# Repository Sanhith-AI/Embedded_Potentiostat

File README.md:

# Embedded_Potentiostat
This project mainly focuses on the development and testing of an embedded potentiostat system that can perform electrochemistry methods like Cyclic voltammetry, Square wave voltammetry, Differential pulse voltammetry, and Impedance spectroscopy.
This project includes the circuit design and PCB design of a potentiostat and power supply using Eagle Autodesk software.
The software implementation includes driver development for SPI, UART, TIMERS, DACs, and ADCs of the STM32F303ZETx microcontroller using STM32cubeIDE as well as Eclipse IDE. Along with driver development, electrochemical methods and digital signal processing methods were implemented using a microcontroller and Matlab.
Moreover, a graphic user interface (GUI) was implemented using C# and Visual Studio to automate the measurement process of the developed potentiostat.

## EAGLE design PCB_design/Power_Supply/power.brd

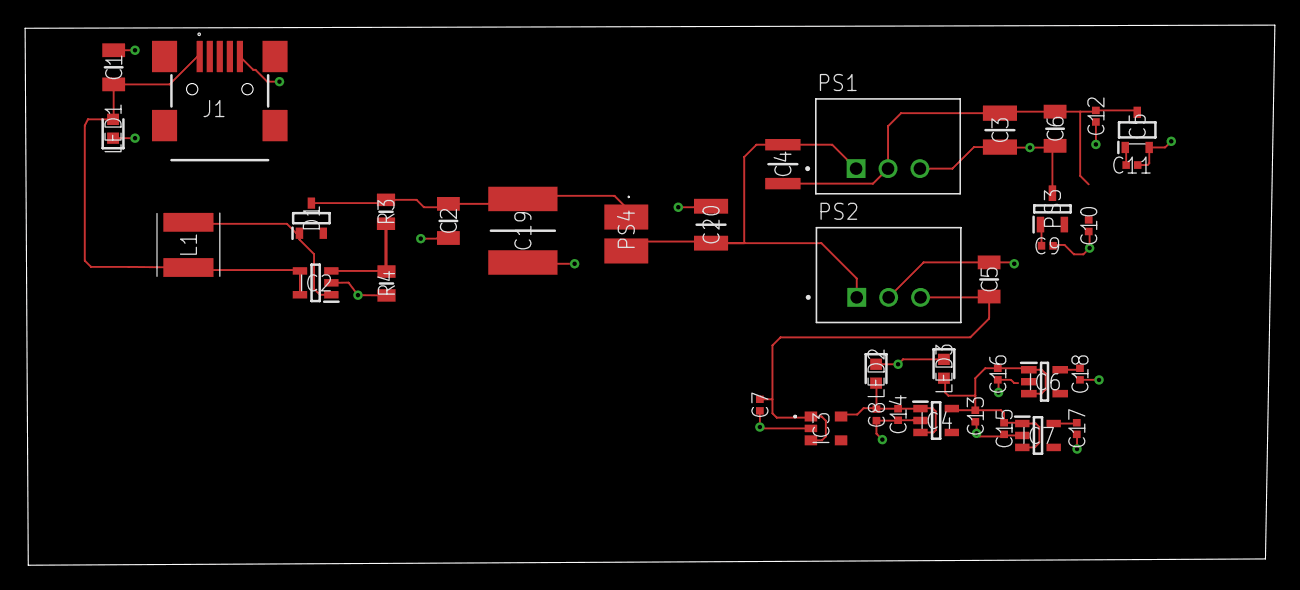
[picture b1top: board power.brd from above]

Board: 2 copper layers, 99.5 x 43.0 mm, 38 parts (0 on the bottom side), 14 nets.

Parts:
C1, C2, C5, C6: LMF316AB7475KLHT; CAPC3216X180N
C3: LMF325B7106KMHP; CAPC3225X270N
C4: GRJ32ER71H106KE11L; CAPC3225X280N
C7, C8, C9, C10, C11, C12, C13, C14, C15, C16, C17, C18: GRM155R70J105KA12D; CAPC1005X55N
C19: KRM55QR72A106KH01L; CAPC6153X390N
C20: 12101C335KAT2A; CAPC3325X279N
D1: BAT54CHYFHT116; SOT95P240X115-3N
IC2: LM2703MFX-ADJ_NOPB; SOT95P280X145-5N
IC3: TCR2EF50,LM_CT; TCR2EF50LMCT
IC4: ADM7160AUJZ-2.5-R7; SOT95P280X100-5N
IC5: XC6902N251MR-G; SOT95P280X130-3N
IC6: NCV8114ASN165T1G; SOT95P275X110-5N
IC7: NCP163ASN150T1G; SOT95P280X145-5N
J1: 65100516121
L1: VLS5045EX-100M-H; VLS5045EX330M
LED1, LED2: LT_Q39G-Q1OO-25-1; LEDC1608X40N
LED3: LB_Q39E-N1OO-35-1; LEDC1608X40N
PS1, PS2: R-786.5-0.5; CONV_R-786.5-0.5
PS3: TC595002ECBTR; SOT95P275X130-3N
PS4: RLS-397; RLS397
R3, R4: TNPW080527K4BEEN; RESC2012X55N

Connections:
1.5V: C17.1, IC7.5
1.65V: C18.1, IC6.5
2.5V: C13.1, C15.1, C16.1, IC4.5, IC6.1, IC6.3, IC7.1, IC7.3, LED3.2
5V: C8.1, C14.1, IC3.5, IC4.1, IC4.3, LED2.2
6.5V: C5.1, C7.1, IC3.1, IC3.3, PS2.3
-2.5V: C11.1, IC5.1
-5V: C9.2, PS3.1
-6.5V: C3.2, C4.2, C6.1, C10.2, C12.1, IC5.3, PS1.2, PS3.2
GND: C1.2, C2.2, C3.1, C5.2, C6.2, C7.2, C8.2, C9.1, C10.1, C11.2, C12.2, C13.2, C14.2, C15.2, C16.2, C17.2, C18.2, C19.2, C20.2, IC2.2, IC3.2, IC4.2, IC5.2, IC7.2, J1.5, LED1.1, LED2.1, LED3.1, PS1.3, PS2.2, PS3.3, R4.2
IN: C2.1, C19.1, D1.3, PS4.1, R3.2
unnamed: IC2.3, R3.1, R4.1
unnamed: C4.1, C20.1, PS1.1, PS2.1, PS4.2
unnamed: D1.1, IC2.1, L1.2
VIN: C1.1, IC2.4, IC2.5, J1.1, L1.1, LED1.2

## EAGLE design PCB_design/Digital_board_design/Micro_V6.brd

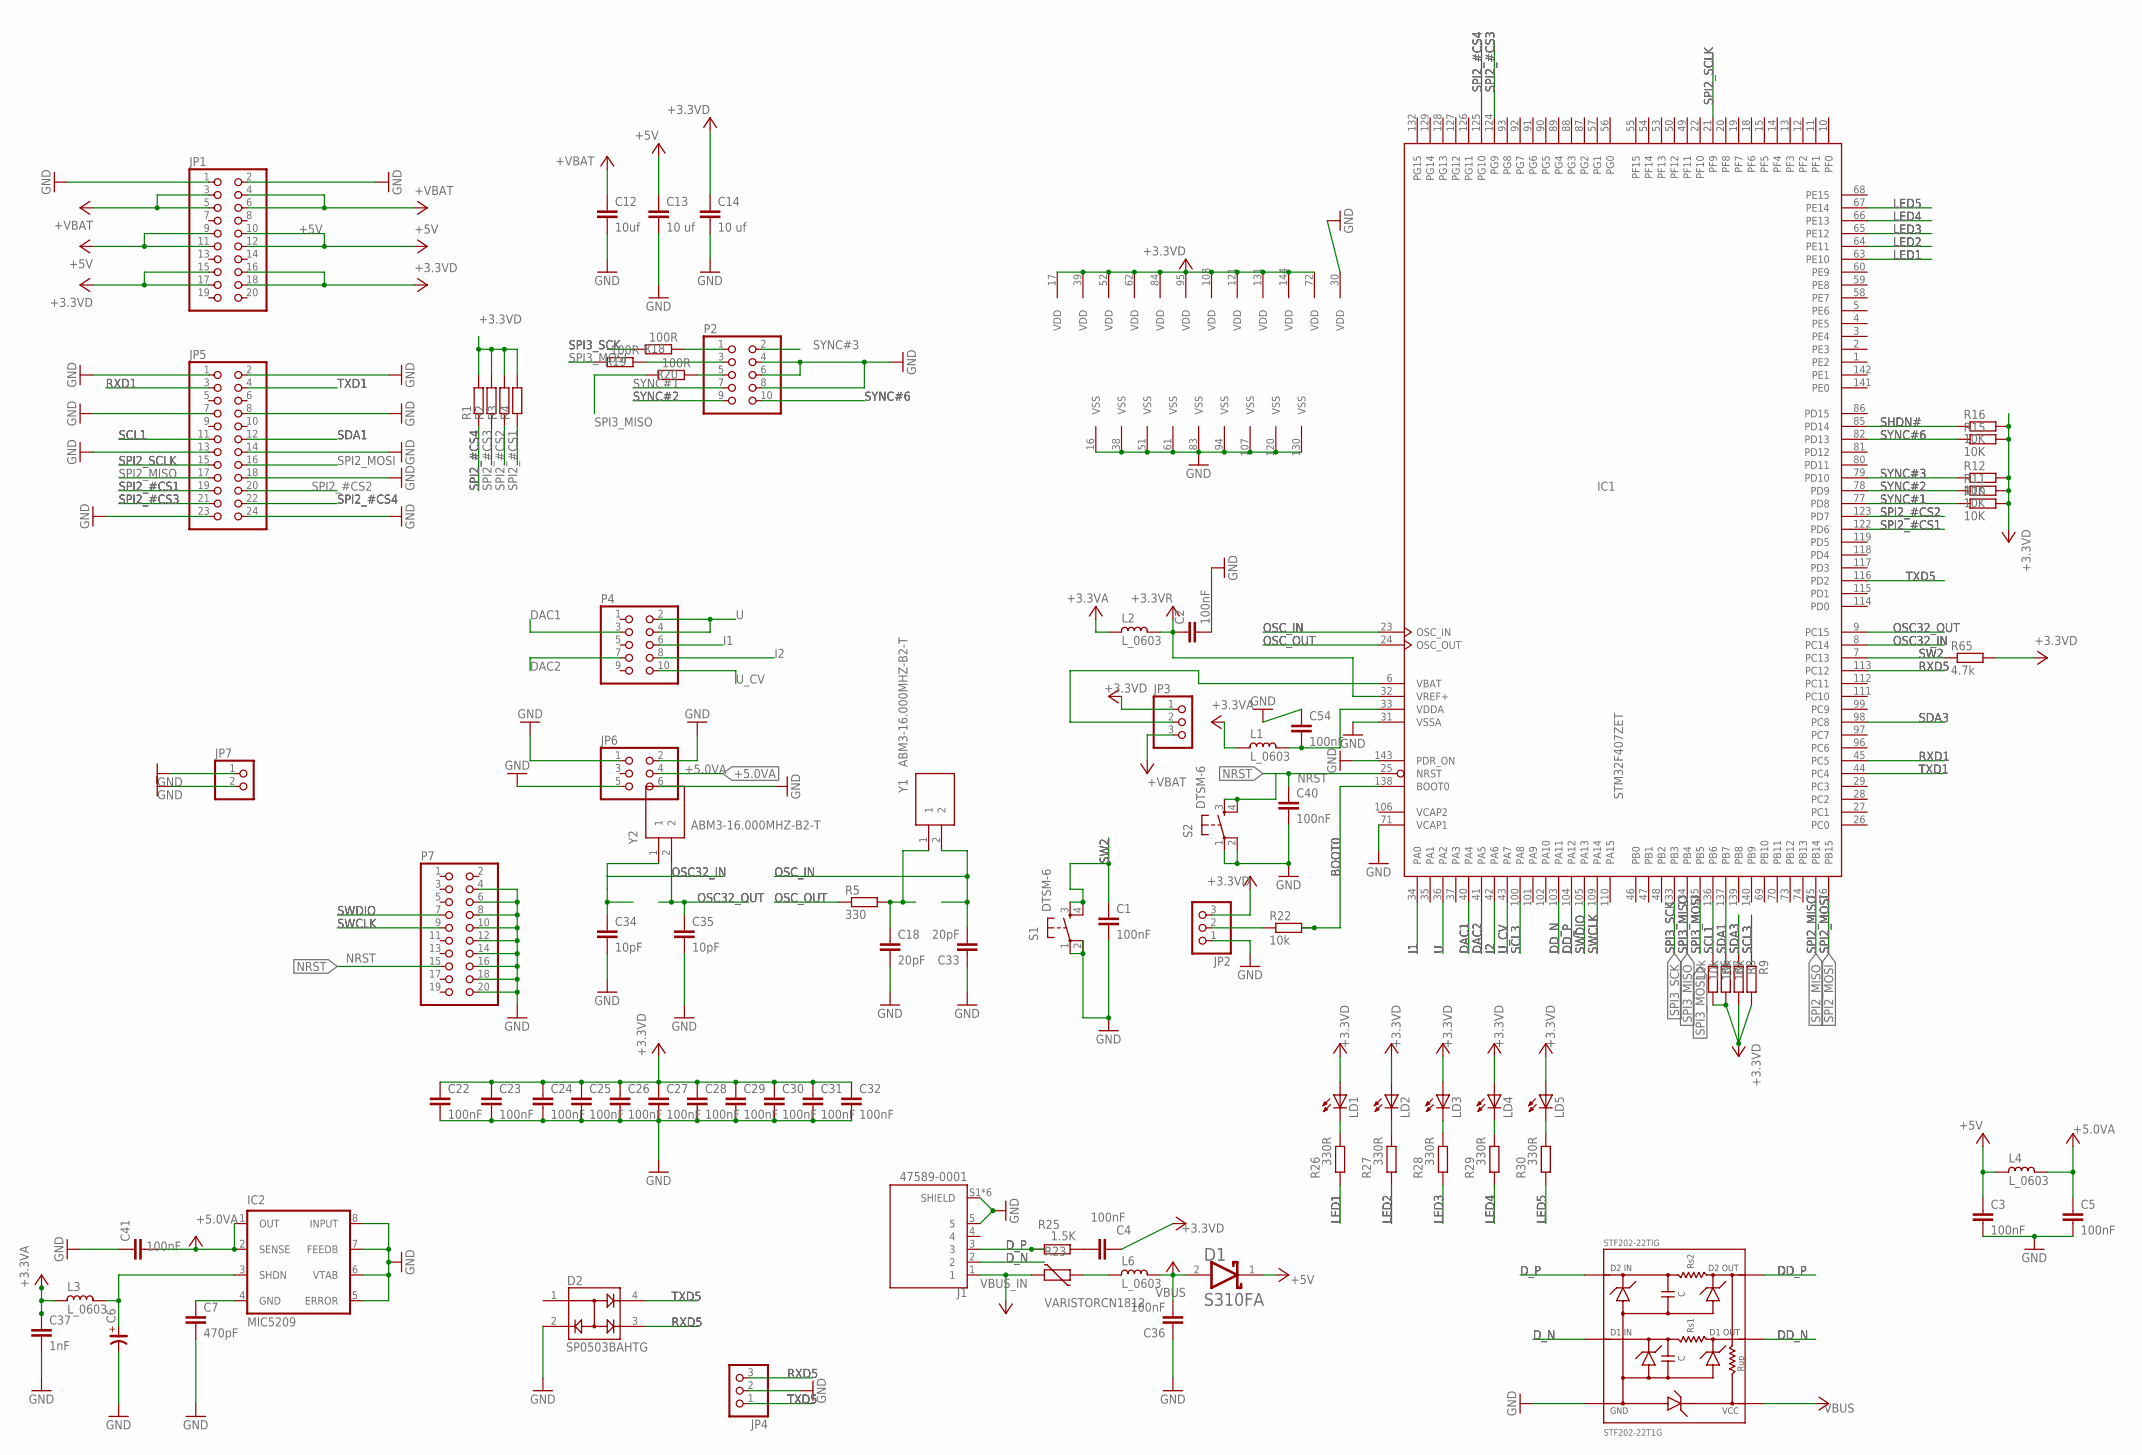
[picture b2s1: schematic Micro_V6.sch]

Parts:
C1, C2, C3, C4, C5, C22, C23, C24, C25, C26, C27, C28, C29, C30, C31, C32, C36, C40, C41, C54: 100nF; C0805
C6: CP_SV-A; CSV-A
C7: 470pF; C0805
C12: 10uf; C0805K
C13, C14: 10 uf; C0805K
C18, C33: 20pF; C0805
C34, C35: 10pF; C0805
C37: 1nF; C0805
D1: ON_SEMICONDUCTOR_S310FAON_SEMICONDUCTOR_S310FA_0_0; ON_SEMICONDUCTOR_S310FA_0
D2: SP0503BAHTG; SOT143
IC1: STM32F407ZET; LQFP144
IC2: MIC5209; SO-08
J1: 47589-0001; MOLEX_47589-0001
JP1: PINHD-2X10; 2X10
JP2, JP3, JP4: PINHD-1X3; 1X03
JP5: PINHD-2X12; 2X12
JP6: PINHD-2X3; 2X03
JP7: PINHD-1X2; 1X02
L1, L2, L3, L4, L6: L_0603; L0603
LD1, LD2, LD3, LD4, LD5: LEDSMT1206; 1206
P2, P4: PINHD-2X5; 2X05
P7: PINHD-2X10; 2X10
R1, R2, R3, R4: R-EU_R0603; R0603
R5: 330; R0603
R6, R7, R8, R9, R22: 10k; R0603
R10, R11, R12, R15, R16: 10K; R0603
R18, R19, R20: 100R; R0603
R23: VARISTORCN1812; CT/CN1812
R25: 1.5K; R0603
R26, R27, R28, R29, R30: 330R; R0603
R65: 4.7k; R0603
S1, S2: DTSM-6
STF202-22TIG: STF202-22T1G
Y1, Y2: ABM3-16.000MHZ-B2-T; ABM316000MHZB2T

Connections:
+3.3VA: C37.1, L1.2, L2.2, L3.2
+3.3VD: C4.1, C14.1, C22.1, C23.1, C24.1, C25.1, C26.1, C27.1, C28.1, C29.1, C30.1, C31.1, C32.1, IC1.17 (VDD), IC1.39 (VDD), IC1.52 (VDD), IC1.62 (VDD), IC1.72 (VDD), IC1.84 (VDD), IC1.95 (VDD), IC1.108 (VDD), IC1.121 (VDD), IC1.131 (VDD), IC1.144 (VDD), JP1.15, JP1.16, JP1.17, JP1.18, JP2.3, JP3.1, LD1.A, LD2.A, LD3.A, LD4.A, LD5.A, R1.2, R2.2, R3.2, R4.2, R6.2, R7.2, R8.2, R9.2, R10.2, R11.2, R12.2, R15.2, R16.2, R65.2
+3.3VR: C2.1, IC1.32 (VREF+), L2.1
+5.0VA: C5.1, C41.2, IC2.1 (OUT), IC2.2 (SENSE), JP6.4, L4.1
+5V: C3.1, C13.1, D1.1 (CATHODE), JP1.9, JP1.10, JP1.11, JP1.12, L4.2
+VBAT: C12.1, JP1.3, JP1.4, JP1.5, JP1.6, JP3.3
BOOT0: IC1.138 (BOOT0), R22.2
DAC1: IC1.40 (PA4), P4.3
DAC2: IC1.41 (PA5), P4.7
DD_N: IC1.103 (PA11), STF202-22TIG.2 (D1-IN)
DD_P: IC1.104 (PA12), STF202-22TIG.3 (D2-IN)
D_N: J1.2, STF202-22TIG.5 (D1-OUT)
D_P: J1.3, R25.1, STF202-22TIG.4 (D2-OUT)
GND: C1.2, C2.2, C3.2, C5.2, C6.-, C7.2, C12.2, C13.2, C14.2, C18.2, C22.2, C23.2, C24.2, C25.2, C26.2, C27.2, C28.2, C29.2, C30.2, C31.2, C32.2, C33.1, C34.2, C35.2, C36.1, C37.2, C40.2, C41.1, C54.1, D2.2, IC1.16 (VSS), IC1.30 (VDD), IC1.31 (VSSA), IC1.38 (VSS), IC1.51 (VSS), IC1.61 (VSS), IC1.71 (VCAP1), IC1.83 (VSS), IC1.94 (VSS), IC1.107 (VSS), IC1.120 (VSS), IC1.130 (VSS), IC1.143 (PDR_ON), IC2.5 (ERROR), IC2.6 (VTAB), IC2.7 (FEEDB), IC2.8 (INPUT), J1.5, J1.S1 (SHIELD), J1.S2 (SHIELD), J1.S3 (SHIELD), J1.S4 (SHIELD), J1.S5 (SHIELD), J1.S6 (SHIELD), JP1.1, JP1.2, JP2.1, JP4.2, JP5.1, JP5.2, JP5.7, JP5.8, JP5.13, JP5.14, JP5.18, JP5.23, JP5.24, JP6.1, JP6.2, JP6.5, JP6.6, JP7.1, JP7.2, P2.4, P2.6, P2.8, P7.4, P7.6, P7.8, P7.10, P7.12, P7.14, P7.16, P7.18, P7.20, S1.1, S1.2, S2.1, S2.2, STF202-22TIG.6 (GND)
I1: IC1.34 (PA0), P4.6
I2: IC1.42 (PA6), P4.8
LED1: IC1.63 (PE10), R26.1
LED2: IC1.64 (PE11), R27.1
LED3: IC1.65 (PE12), R28.1
LED4: IC1.66 (PE13), R29.1
LED5: IC1.67 (PE14), R30.1
unnamed: IC1.6 (VBAT), JP3.2
unnamed: C54.2, IC1.33 (VDDA), L1.1
unnamed: P2.3, R19.1
unnamed: P2.5, R20.1
unnamed: L6.2, R23.1
unnamed: P2.1, R18.1
unnamed: C18.1, R5.2, Y1.1
unnamed: JP2.2, R22.1
unnamed: C6.+, IC2.3 (SHDN), L3.1
unnamed: C7.1, IC2.4 (GND)
unnamed: C4.2, R25.2
unnamed: LD1.C, R26.2
unnamed: LD2.C, R27.2
unnamed: LD3.C, R28.2
unnamed: LD4.C, R29.2
unnamed: LD5.C, R30.2
NRST: C40.1, IC1.25 (NRST), P7.15, S2.3, S2.4
OSC32_IN: C34.1, IC1.8 (PC14), Y2.1
OSC32_OUT: C35.1, IC1.9 (PC15), Y2.2
OSC_IN: C33.2, IC1.23 (OSC_IN), Y1.2
OSC_OUT: IC1.24 (OSC_OUT), R5.1
RXD1: IC1.45 (PC5), JP5.3
RXD5: D2.3, IC1.113 (PC12), JP4.3
SCL1: IC1.136 (PB6), JP5.11, R6.1
SCL3: IC1.100 (PA8), R9.1
SDA1: IC1.137 (PB7), JP5.12, R7.1
SDA3: IC1.98 (PC8), R8.1
SHDN#: IC1.85 (PD14), R16.1
SPI2_#CS1: IC1.122 (PD6), JP5.19, R4.1
SPI2_#CS2: IC1.123 (PD7), JP5.20, R3.1
SPI2_#CS3: IC1.124 (PG9), JP5.21, R2.1
SPI2_#CS4: IC1.125 (PG10), JP5.22, R1.1
SPI2_MISO: IC1.75 (PB14), JP5.17
SPI2_MOSI: IC1.76 (PB15), JP5.16
SPI2_SCLK: IC1.21 (PF9), JP5.15
SPI3_MISO: IC1.134 (PB4), R20.2
SPI3_MOSI: IC1.135 (PB5), R19.2
SPI3_SCK: IC1.133 (PB3), R18.2
SW2: C1.1, IC1.7 (PC13), R65.1, S1.3, S1.4
SWCLK: IC1.109 (PA14), P7.9
SWDIO: IC1.105 (PA13), P7.7
SYNC#1: IC1.77 (PD8), P2.7, R10.1
SYNC#2: IC1.78 (PD9), P2.9, R11.1
SYNC#3: IC1.79 (PD10), P2.2, R12.1
SYNC#6: IC1.82 (PD13), P2.10, R15.1
TXD1: IC1.44 (PC4), JP5.4
TXD5: D2.4, IC1.116 (PD2), JP4.1
U: IC1.36 (PA2), P4.2, P4.4
U_CV: IC1.43 (PA7), P4.10
VBUS: C36.2, D1.2 (ANODE), L6.1, STF202-22TIG.1 (VCC)
VBUS_IN: J1.1, R23.2
VCAP2: IC1.106 (VCAP2)

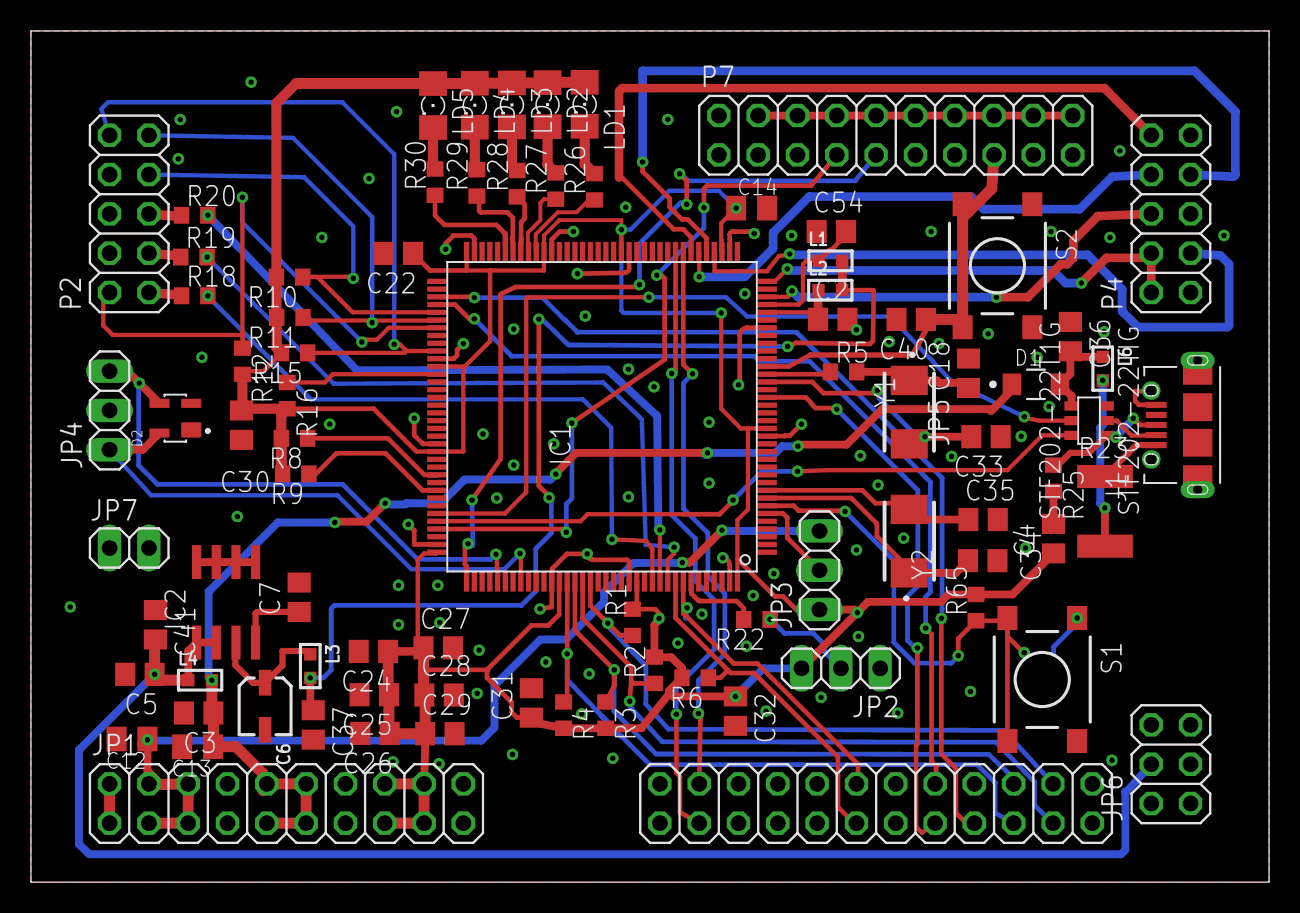
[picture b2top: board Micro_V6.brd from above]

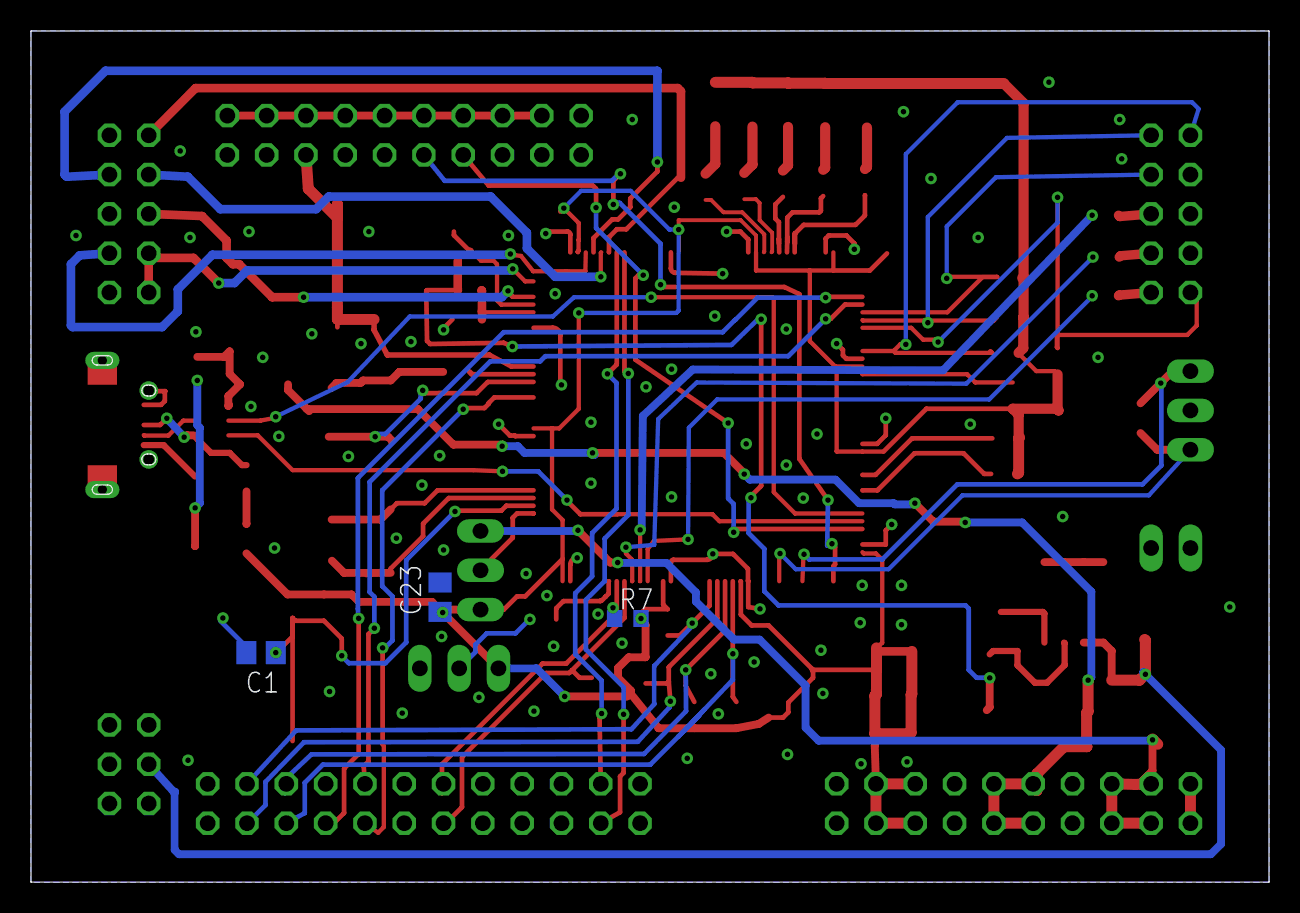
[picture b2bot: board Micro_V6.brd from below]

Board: 2 copper layers, 80.0 x 55.0 mm, 86 parts (3 on the bottom side), 72 nets.

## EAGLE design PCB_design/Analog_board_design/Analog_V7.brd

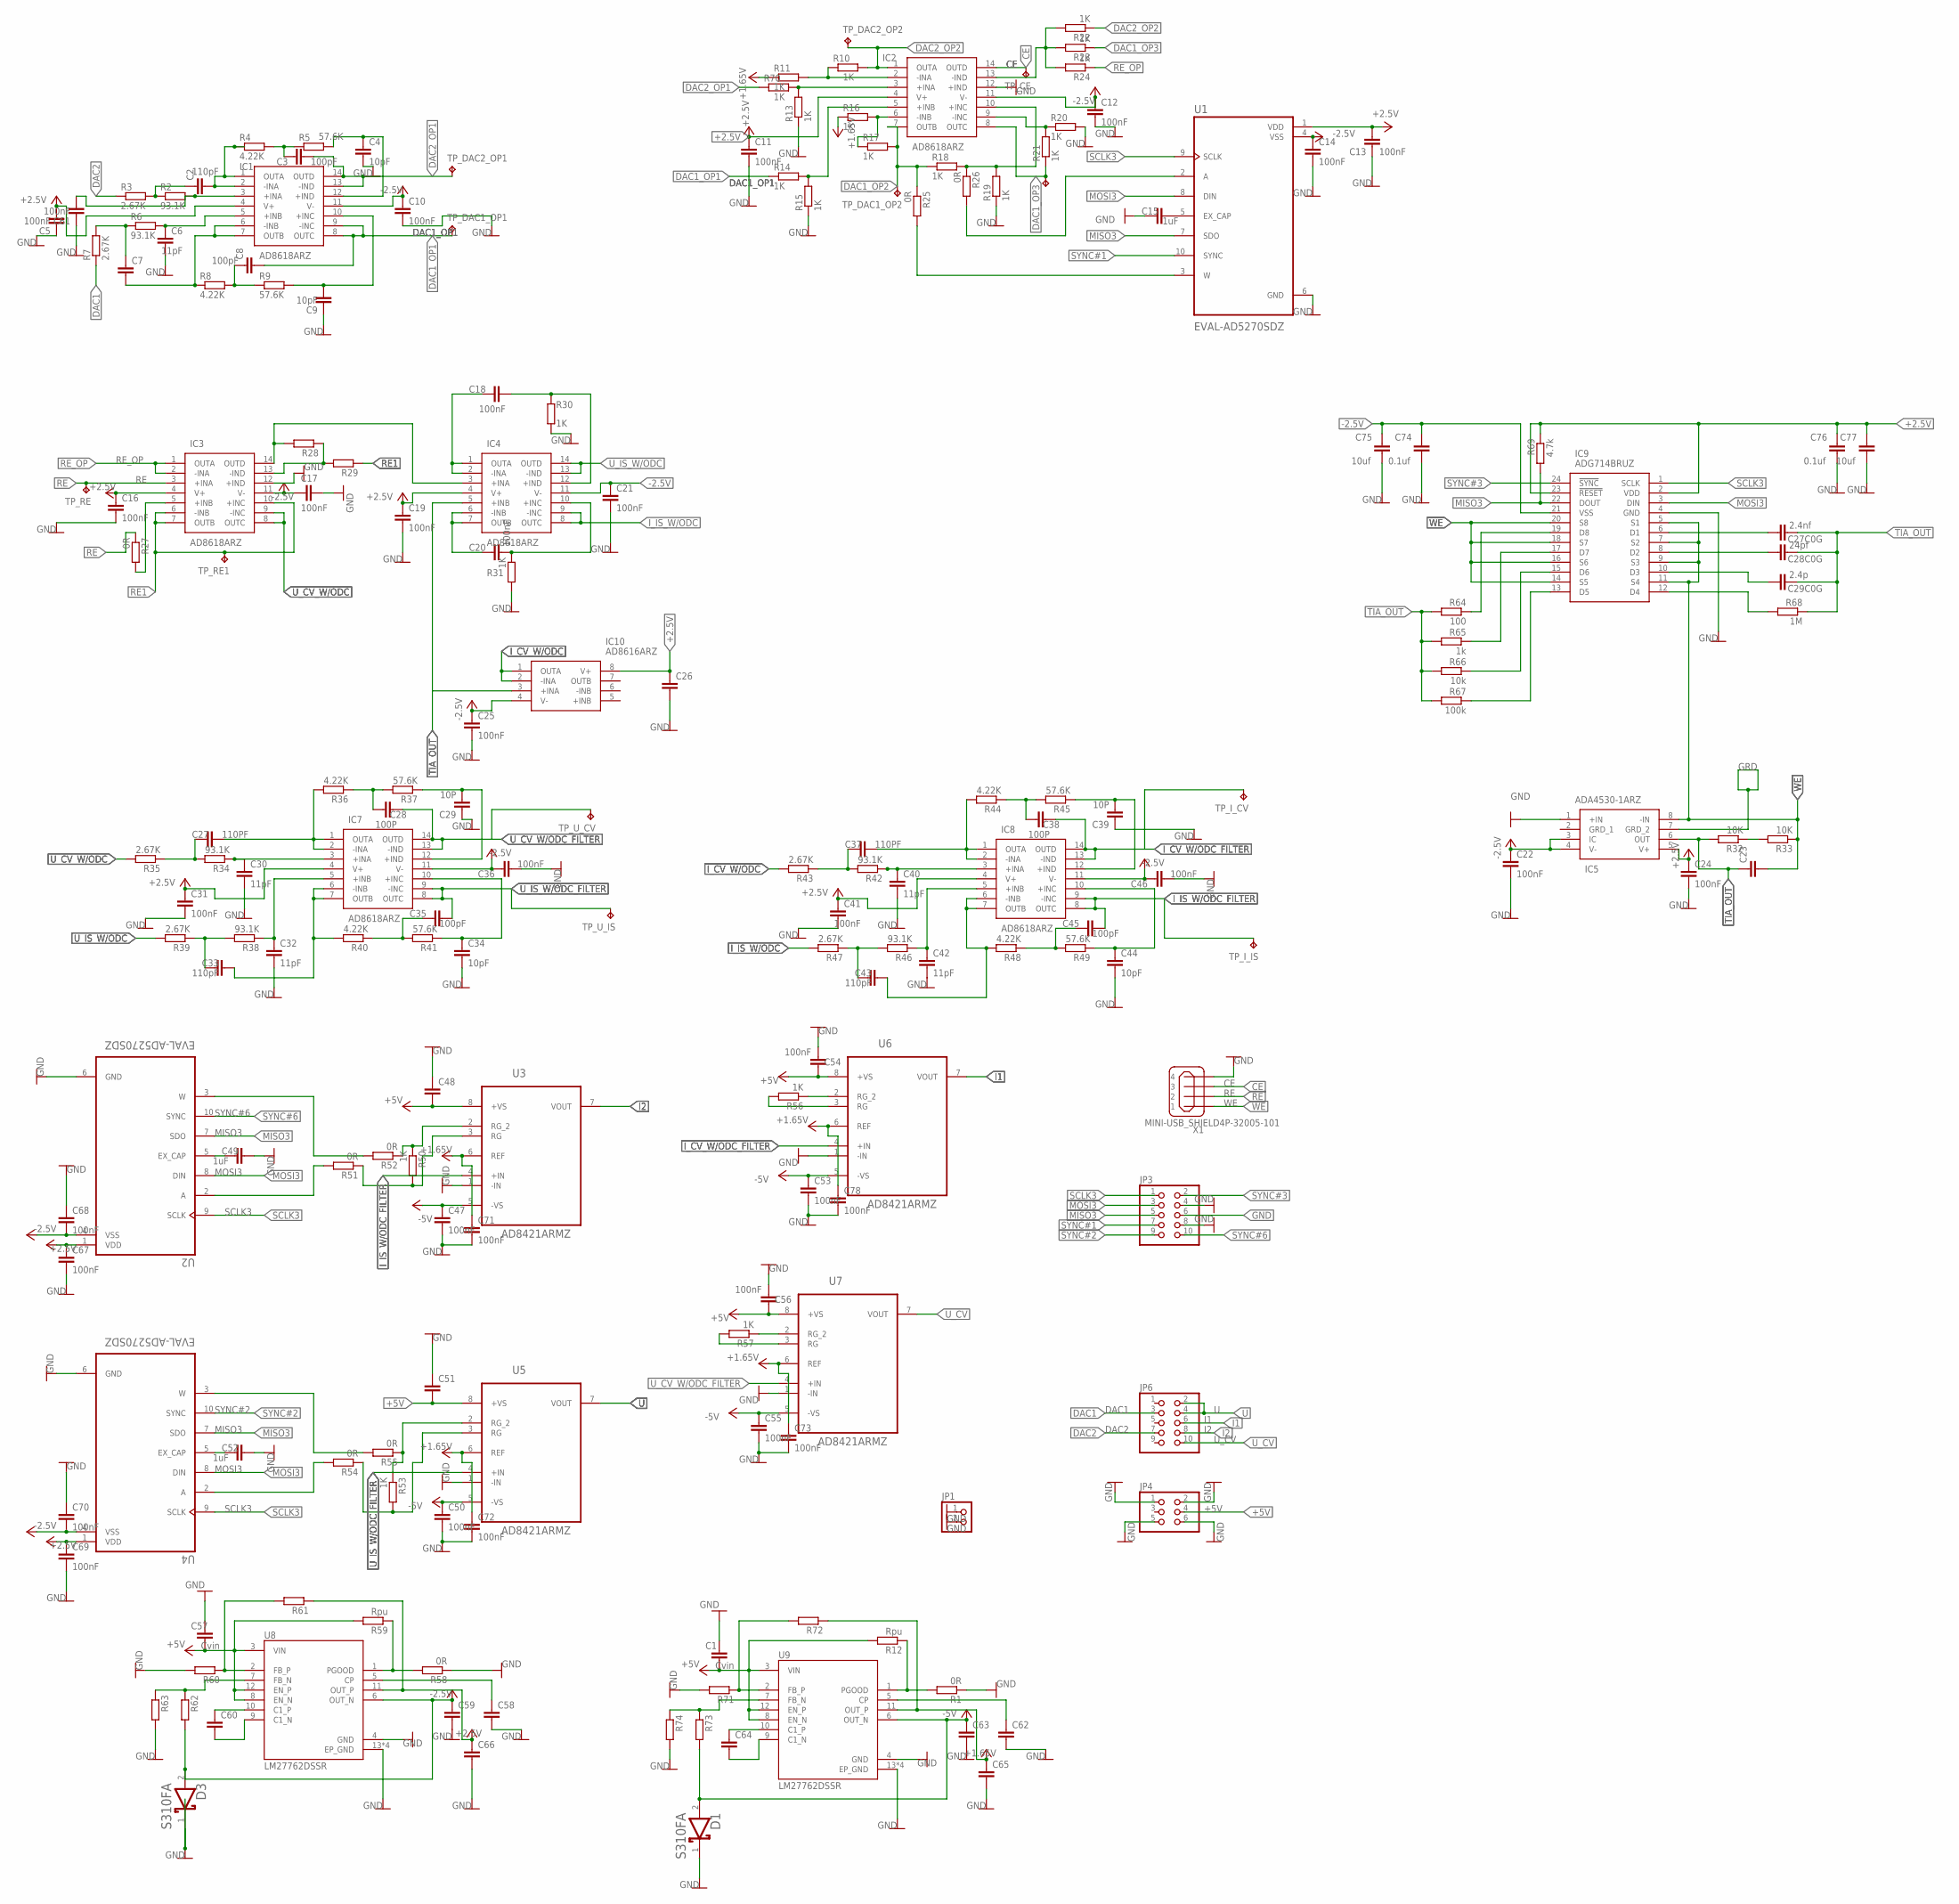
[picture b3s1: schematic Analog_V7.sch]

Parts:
C1, C57: Cvin; C0805
C2, C33, C43: 110pF; C0805
C3, C8, C35, C45: 100pF; C0805
C4, C9, C34, C44: 10pF; C0805
C5, C10, C11, C12, C13, C14, C16, C17, C18, C19, C20, C21, C22, C24, C25, C31, C36, C41, C46, C47, C50, C53, C54, C55, C56, C61, C67, C68, C69, C70, C71, C72, C73, C78: 100nF; C0805
C6, C30, C32, C40, C42: 11pF; C0805
C7, C23, C26, C48, C51, C58, C59, C60, C62, C63, C64, C65, C66: C-EUC0805; C0805
C15, C49, C52: 1uF; C0805
C27, C37: 110PF; C0805
C27C0G: 2.4nf; C0603
C28, C38: 100P; C0805
C28C0G: 24pf; C0603
C29, C39: 10P; C0805
C29C0G: 2.4p; C0603
C74, C76: 0.1uf; C0603
C75, C77: 10uf; C0603
D1, D3: ON_SEMICONDUCTOR_S310FAON_SEMICONDUCTOR_S310FA_0_0; ON_SEMICONDUCTOR_S310FA_0
IC1, IC2, IC3, IC4, IC7, IC8: AD8618ARZ; SOIC127P600X175-14N
IC5: ADA4530-1ARZ; SOIC127P600X175-8N
IC9: ADG714BRUZ; SOP65P640X120-24N
IC10: AD8616ARZ; SOIC127P600X175-8N
JP1: PINHD-1X2; 1X02
JP3, JP6: PINHD-2X5; 2X05
JP4: PINHD-2X3; 2X03
R1, R25, R26, R27, R51, R52, R54, R55, R58: 0R; R0603
R2, R6, R34, R38, R42, R46: 93.1K; R0603
R3, R7, R35, R39, R43, R47: 2.67K; R0603
R4, R8, R36, R40, R44, R48: 4.22K; R0603
R5, R9, R37, R41, R45, R49: 57.6K; R0603
R10, R11, R13, R14, R15, R16, R17, R18, R19, R20, R21, R22, R23, R24, R30, R31, R50, R53, R56, R57, R70: 1K; R0603
R12, R59: Rpu; R0603
R28, R29, R60, R61, R62, R63, R71, R72, R73, R74: R-EU_R0603; R0603
R32, R33: 10K; R0603
R64: 100; R0603
R65: 1k; R0603
R66: 10k; R0603
R67: 100k; R0603
R68: 1M; R0603
R69: 4.7k; R0603
TP_CE: TPB1,27; B1,27
TP_DAC1_OP1: TP_DAC1_OP1; B1,27
TP_DAC1_OP2, TP_DAC1_OP3: TPB1,27; B1,27
TP_DAC2_OP1: TP_DAC2_OP1; B1,27
TP_DAC2_OP2: TP_DAC2_OP2; B1,27
TP_I_CV: TPB1,27; B1,27
TP_I_IS: TPB1,27; B1,27
TP_RE, TP_RE1: TPB1,27; B1,27
TP_U_CV: TPB1,27; B1,27
TP_U_IS: TPB1,27; B1,27
U1, U2, U4: EVAL-AD5270SDZ; SOP50P490X110-10N
U3, U5, U6, U7: AD8421ARMZ; SOP65P490X110-8N
U8, U9: LM27762DSSR; VREG_LM27762DSSR
X1: MINI-USB_SHIELD4P-32005-101; 32005-101

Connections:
+1.65V: C65.1, C71.1, C72.1, C73.1, C78.1, R11.1, R16.1, R72.1, U3.6 (REF), U5.6 (REF), U6.6 (REF), U7.6 (REF), U9.11 (OUT_P)
+2.5V: C5.2, C11.1, C13.2, C16.1, C19.1, C24.1, C26.1, C31.1, C41.1, C66.1, C67.1, C69.1, C76.1, C77.1, IC1.4 (V+), IC2.4 (V+), IC3.4 (V+), IC4.4 (V+), IC5.5 (V+), IC7.4 (V+), IC8.4 (V+), IC9.2 (VDD), IC9.23 (!RESET), IC10.8 (V+), R61.1, R69.1, U1.1 (VDD), U2.1 (VDD), U4.1 (VDD), U8.11 (OUT_P)
+5V: C1.2, C48.2, C51.2, C54.2, C56.2, C57.2, JP4.4, R12.2, R59.2, U3.8 (+VS), U5.8 (+VS), U6.8 (+VS), U7.8 (+VS), U8.3 (VIN), U8.8 (EN_N), U8.12 (EN_P), U9.3 (VIN), U9.8 (EN_N), U9.12 (EN_P)
-2.5V: C10.1, C12.1, C14.1, C17.1, C21.1, C22.1, C25.1, C36.2, C46.2, C59.1, C68.2, C70.2, C74.1, C75.1, D3.2 (ANODE), IC1.11 (V-), IC2.11 (V-), IC3.11 (V-), IC4.11 (V-), IC5.3 (IC), IC5.4 (V-), IC7.11 (V-), IC8.11 (V-), IC9.21 (VSS), IC10.4 (V-), R62.2, U1.4 (VSS), U2.4 (VSS), U4.4 (VSS), U8.6 (OUT_N)
-5V: C47.1, C50.1, C53.1, C55.1, C63.1, D1.2 (ANODE), R73.2, U3.5 (-VS), U5.5 (-VS), U6.5 (-VS), U7.5 (-VS), U9.6 (OUT_N)
CE: IC2.14 (OUTD), TP_CE.TP, X1.3
DAC1: JP6.3, R7.1
DAC1_OP1: C8.2, IC1.8 (OUTC), IC1.9 (-INC), R14.1, TP_DAC1_OP1.TP
DAC1_OP2: IC2.7 (OUTB), R17.2, R18.1, R25.1, TP_DAC1_OP2.TP
DAC1_OP3: IC2.8 (OUTC), R21.1, R23.1, TP_DAC1_OP3.TP
DAC2: JP6.7, R3.1
DAC2_OP1: C3.2, IC1.13 (-IND), IC1.14 (OUTD), R70.1, TP_DAC2_OP1.TP
DAC2_OP2: IC2.1 (OUTA), R10.2, R22.1, TP_DAC2_OP2.TP
GND: C1.1, C4.2, C5.1, C6.2, C9.1, C10.2, C11.2, C12.2, C13.1, C14.2, C15.1, C16.2, C17.2, C19.2, C21.2, C22.2, C24.2, C25.2, C26.2, C29.1, C30.2, C31.2, C32.2, C34.2, C36.1, C39.1, C40.2, C41.2, C42.2, C44.2, C46.1, C47.2, C48.1, C49.2, C50.2, C51.1, C52.2, C53.2, C54.1, C55.2, C56.1, C57.1, C58.2, C59.2, C61.1, C62.2, C63.2, C65.2, C66.2, C67.2, C68.1, C69.2, C70.1, C71.2, C72.2, C73.2, C74.2, C75.2, C76.2, C77.2, C78.2, D1.1 (CATHODE), D3.1 (CATHODE), IC2.12 (+IND), IC3.12 (+IND), IC5.1 (+IN), IC9.4 (GND), JP1.1, JP1.2, JP3.4, JP3.6, JP3.8, JP4.1, JP4.2, JP4.5, JP4.6, R1.1, R13.1, R15.1, R19.1, R20.2, R30.2, R31.2, R58.1, R60.2, R63.2, R71.2, R74.2, U1.6 (GND), U2.6 (GND), U3.1 (-IN), U5.1 (-IN), U6.1 (-IN), U7.1 (-IN), U8.4 (GND), U8.13 (EP_GND), U8.13.1 (EP_GND), U8.13.2 (EP_GND), U8.13.3 (EP_GND), U9.4 (GND), U9.13 (EP_GND), U9.13.1 (EP_GND), U9.13.2 (EP_GND), U9.13.3 (EP_GND), X1.4
GND1: U4.6 (GND)
GRD: IC5.7 (GRD_2)
I1: JP6.6, U6.7 (VOUT)
I2: JP6.8, U3.7 (VOUT)
I_CV_W/ODC: IC10.1 (OUTA), IC10.2 (-INA), R43.2
I_CV_W/ODC_FILTER: C38.2, IC8.13 (-IND), IC8.14 (OUTD), TP_I_CV.TP, U6.4 (+IN)
I_IS_W/ODC: IC4.8 (OUTC), IC4.9 (-INC), R47.2
I_IS_W/ODC_FILTER: C45.2, IC8.8 (OUTC), IC8.9 (-INC), TP_I_IS.TP, U3.4 (+IN)
MISO3: IC9.22 (DOUT), JP3.5, R69.2, U1.7 (SDO), U2.7 (SDO), U4.7 (SDO)
MOSI3: IC9.3 (DIN), JP3.3, U1.8 (DIN), U2.8 (DIN), U4.8 (DIN)
unnamed: C2.2, IC1.1 (OUTA), IC1.2 (-INA), R4.1
unnamed: C7.2, IC1.6 (-INB), IC1.7 (OUTB), R8.1
unnamed: IC2.9 (-INC), R20.1, R21.2
unnamed: C61.2, IC1.3 (+INA), R2.2
unnamed: C3.1, R4.2, R5.1
unnamed: IC2.3 (+INA), R13.2, R70.2
unnamed: C6.1, IC1.5 (+INB), R6.2
unnamed: C7.1, R6.1, R7.2
unnamed: IC2.2 (-INA), R10.1, R11.2
unnamed: C8.1, R8.2, R9.1
unnamed: C9.2, IC1.10 (+INC), R9.2
unnamed: IC2.5 (+INB), R14.2, R15.2
unnamed: IC2.6 (-INB), R16.2, R17.1
unnamed: C4.1, IC1.12 (+IND), R5.2
unnamed: IC2.13 (-IND), R22.2, R23.2, R24.2
unnamed: R25.2, U1.3 (W)
unnamed: R26.2, U1.2 (A)
unnamed: C15.2, U1.5 (EX_CAP)
unnamed: IC3.5 (+INB), R27.2
unnamed: IC3.14 (OUTD), IC4.3 (+INA), R28.2
unnamed: IC3.13 (-IND), R28.1, R29.2
unnamed: C18.1, IC4.1 (OUTA), IC4.2 (-INA)
unnamed: C20.1, IC4.6 (-INB), IC4.7 (OUTB)
unnamed: C27.2, IC7.1 (OUTA), IC7.2 (-INA), R36.2
unnamed: IC9.19 (D8), R64.1
unnamed: R32.1, R33.2
unnamed: C30.1, IC7.3 (+INA), R34.1
unnamed: C27.1, R34.2, R35.1
unnamed: C28.1, R36.1, R37.2
unnamed: C33.2, IC7.6 (-INB), IC7.7 (OUTB), R40.2
unnamed: C33.1, R38.2, R39.1
unnamed: C37.2, IC8.1 (OUTA), IC8.2 (-INA), R44.2
unnamed: C32.1, IC7.5 (+INB), R38.1
unnamed: C35.1, R40.1, R41.2
unnamed: C34.1, IC7.10 (+INC), R41.1
unnamed: C40.1, IC8.3 (+INA), R42.1
unnamed: C37.1, R42.2, R43.1
unnamed: C38.1, R44.1, R45.2
unnamed: C43.2, IC8.6 (-INB), IC8.7 (OUTB), R48.2
unnamed: C43.1, R46.2, R47.1
unnamed: C42.1, IC8.5 (+INB), R46.1
unnamed: C45.1, R48.1, R49.2
unnamed: C44.1, IC8.10 (+INC), R49.1
unnamed: R50.1, R52.1, U3.2 (RG_2)
unnamed: R50.2, R51.1, U3.3 (RG)
unnamed: R52.2, U2.3 (W)
unnamed: R51.2, U2.2 (A)
unnamed: R56.1, U6.2 (RG_2)
unnamed: C49.1, U2.5 (EX_CAP)
unnamed: R53.1, R55.1, U5.2 (RG_2)
unnamed: C64.1, U9.10 (C1_P)
unnamed: R55.2, U4.3 (W)
unnamed: R54.2, U4.2 (A)
unnamed: R56.2, U6.3 (RG)
unnamed: C52.1, U4.5 (EX_CAP)
unnamed: R57.1, U7.2 (RG_2)
unnamed: C18.2, IC4.12 (+IND), R30.1
unnamed: R57.2, U7.3 (RG)
unnamed: IC9.17 (D7), R65.1
unnamed: IC9.15 (D6), R66.1
unnamed: IC9.13 (D5), R67.1
unnamed: C27C0G.2, IC9.6 (D1)
unnamed: C60.1, U8.10 (C1_P)
unnamed: C60.2, U8.9 (C1_N)
unnamed: C28C0G.2, IC9.8 (D2)
unnamed: C29C0G.2, IC9.10 (D3)
unnamed: IC9.12 (D4), R68.2
unnamed: C20.2, IC4.10 (+INC), R31.1
unnamed: C64.2, U9.9 (C1_N)
unnamed: R71.1, R72.2, U9.2 (FB_P)
unnamed: IC2.10 (+INC), R18.2, R19.2, R26.1
unnamed: R1.2, R12.1, U9.1 (PGOOD)
unnamed: C2.1, R2.1, R3.2
unnamed: C29.2, IC7.12 (+IND), R37.1
unnamed: C39.2, IC8.12 (+IND), R45.1
unnamed: R53.2, R54.1, U5.3 (RG)
unnamed: R60.1, R61.2, U8.2 (FB_P)
unnamed: R58.2, R59.1, U8.1 (PGOOD)
unnamed: C58.1, U8.5 (CP)
unnamed: R62.1, R63.1, U8.7 (FB_N)
unnamed: C62.1, U9.5 (CP)
unnamed: R73.1, R74.1, U9.7 (FB_N)
RE: IC3.3 (+INA), R27.1, TP_RE.TP, X1.2
RE1: IC3.6 (-INB), IC3.7 (OUTB), IC3.10 (+INC), R29.1, TP_RE1.TP
RE_OP: IC3.1 (OUTA), IC3.2 (-INA), R24.1
SCLK3: IC9.1 (SCLK), JP3.1, U1.9 (SCLK), U2.9 (SCLK), U4.9 (SCLK)
SYNC#1: JP3.7, U1.10 (SYNC)
SYNC#2: JP3.9, U4.10 (SYNC)
SYNC#3: IC9.24 (!SYNC), JP3.2
SYNC#6: JP3.10, U2.10 (SYNC)
TIA_OUT: C23.1, C27C0G.1, C28C0G.1, C29C0G.1, IC4.5 (+INB), IC5.6 (OUT), IC10.3 (+INA), R32.2, R64.2, R65.2, R66.2, R67.2, R68.1
U: JP6.2, JP6.4, U5.7 (VOUT)
U_CV: JP6.10, U7.7 (VOUT)
U_CV_W/ODC: IC3.8 (OUTC), IC3.9 (-INC), R35.2
U_CV_W/ODC_FILTER: C28.2, IC7.13 (-IND), IC7.14 (OUTD), TP_U_CV.TP, U7.4 (+IN)
U_IS_W/ODC: IC4.13 (-IND), IC4.14 (OUTD), R39.2
U_IS_W/ODC_FILTER: C35.2, IC7.8 (OUTC), IC7.9 (-INC), TP_U_IS.TP, U5.4 (+IN)
WE: C23.2, IC5.8 (-IN), IC9.5 (S1), IC9.7 (S2), IC9.9 (S3), IC9.11 (S4), IC9.14 (S5), IC9.16 (S6), IC9.18 (S7), IC9.20 (S8), R33.1, X1.1

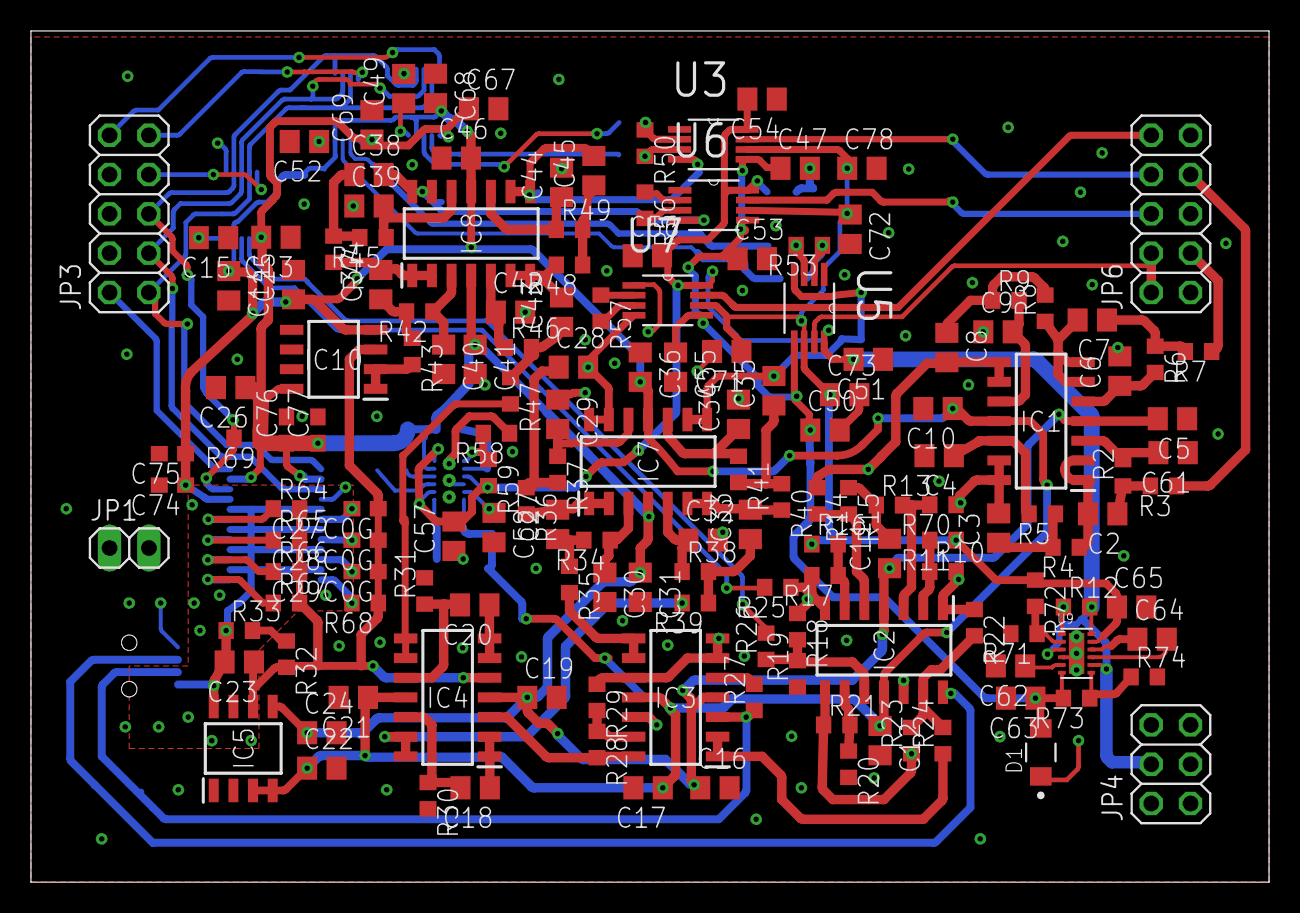
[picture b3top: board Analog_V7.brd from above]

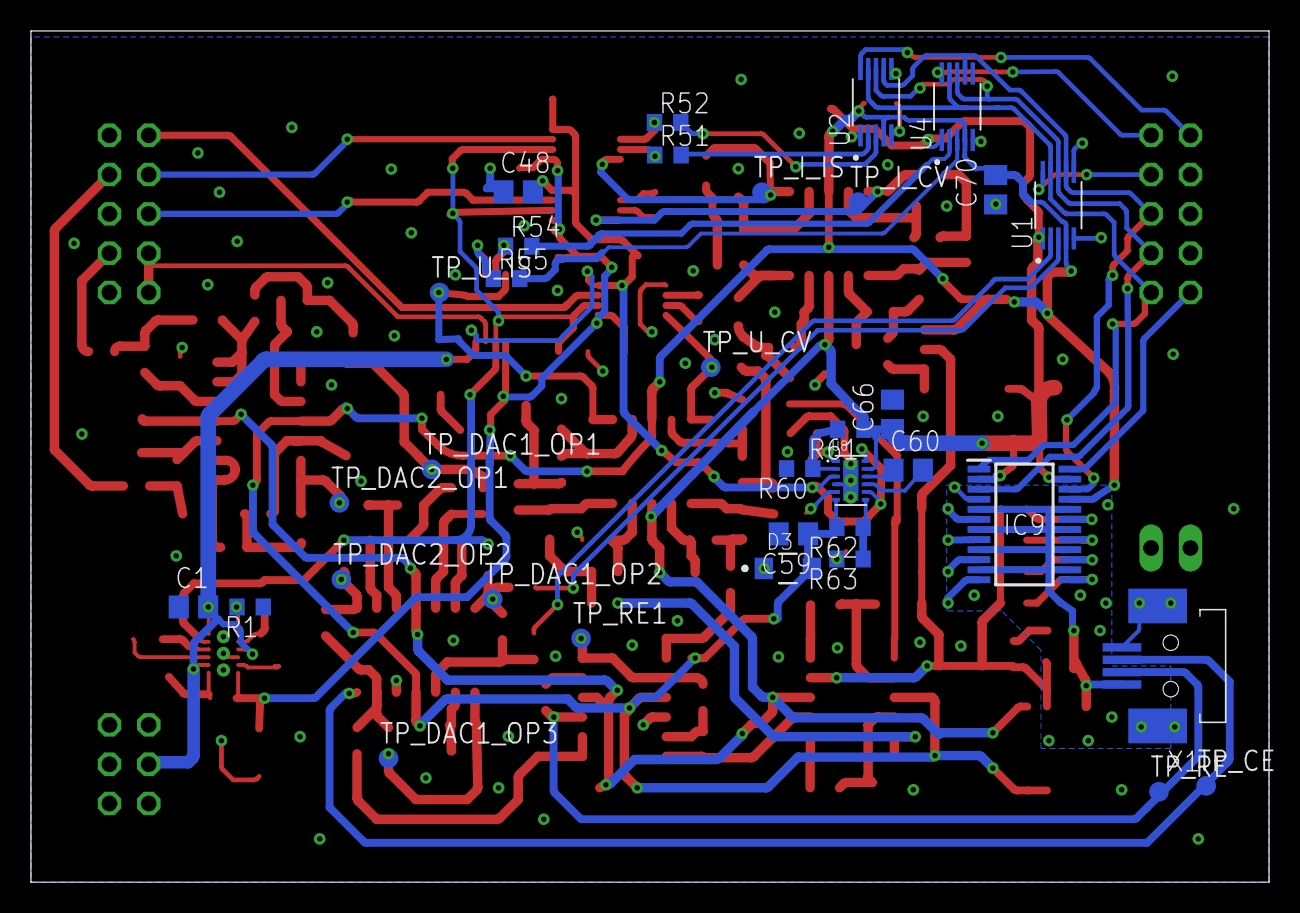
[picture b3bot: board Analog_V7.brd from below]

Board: 2 copper layers, 80.0 x 55.0 mm, 192 parts (34 on the bottom side), 120 nets.

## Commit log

2023-09-08 first commit~

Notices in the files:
parts and their libraries:
rc-master-smd: Copyright (C) 2007, Bob Starr
